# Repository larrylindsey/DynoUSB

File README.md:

DynoUSB
=======

A 5V USB rectifier project in EagleCAD

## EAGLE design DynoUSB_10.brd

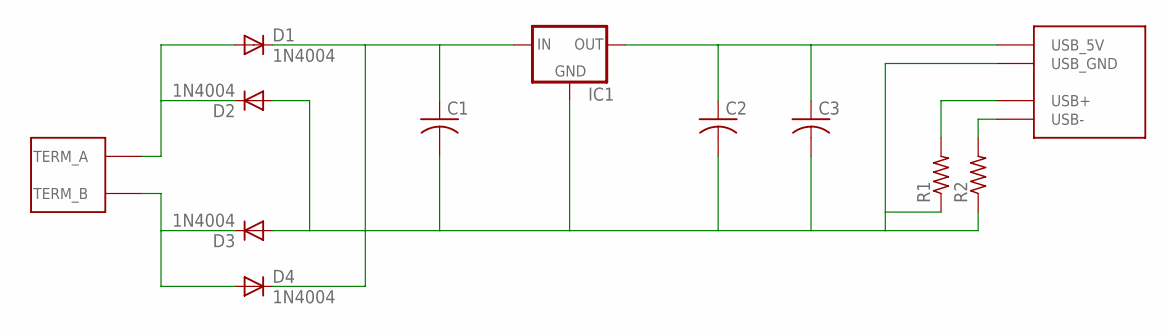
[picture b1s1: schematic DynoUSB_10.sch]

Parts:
C1, C2: C-USC1206; C1206
C3: C-USC3216; C3216
D1, D2, D3, D4: 1N4004; DO41-10
IC1: 78XXL
R1, R2: R-US_M1206; M1206
U$1: SPARKFUN_USB_A; USB_4UCON_18666_318
U$2: SCREW_TERM_2; SCREWTERMINAL-5MM-2

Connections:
unnamed: D1.A, D2.C, U$2.1 (TERM_A)
unnamed: D3.C, D4.A, U$2.2 (TERM_B)
unnamed: C2.1, C3.1, IC1.OUT, U$1.USB_5V
unnamed: C1.1, D1.C, D4.C, IC1.IN
unnamed: C1.2, C2.2, C3.2, D2.A, D3.A, IC1.GND, R1.1, R2.1, U$1.USB_GND
unnamed: R1.2, U$1.USB+
unnamed: R2.2, U$1.USB-

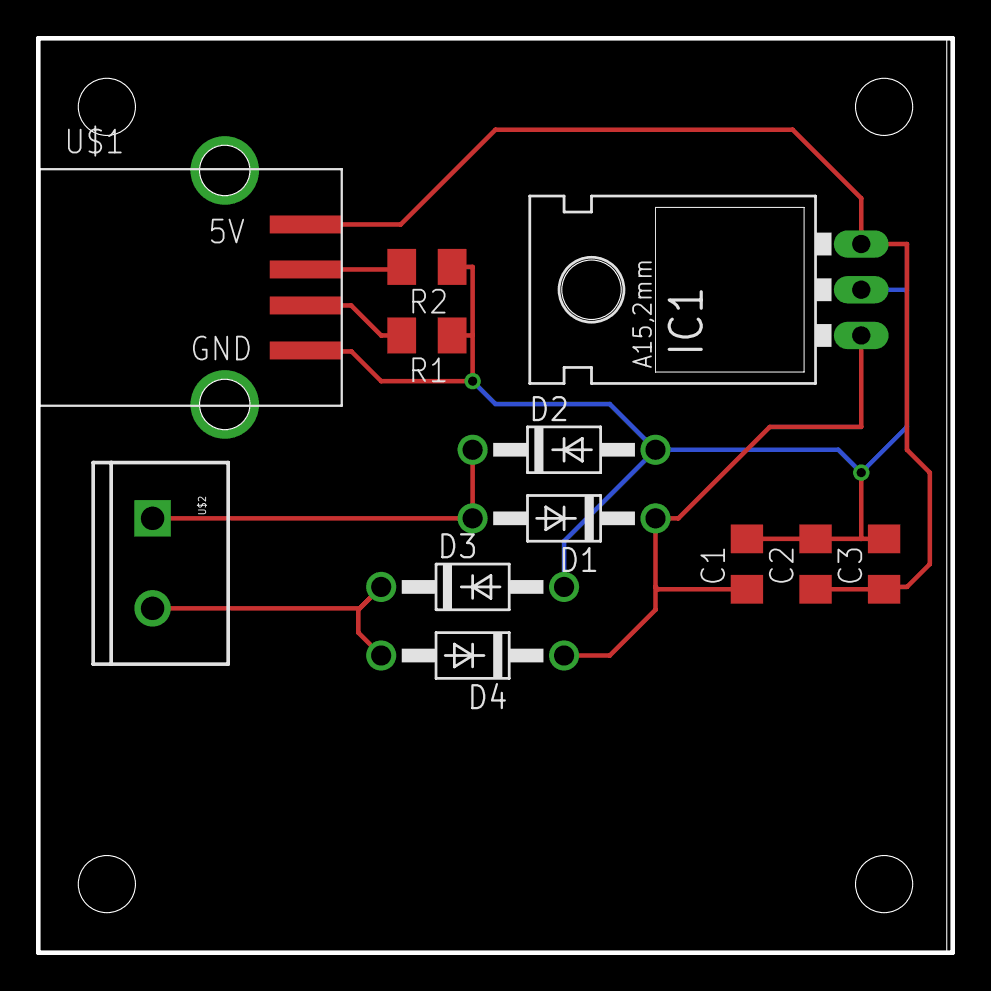
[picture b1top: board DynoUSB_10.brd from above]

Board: 2 copper layers, 50.8 x 50.8 mm, 12 parts (0 on the bottom side), 7 nets.

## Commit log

2014-03-13 DynoUSB version 1.0 first commit
